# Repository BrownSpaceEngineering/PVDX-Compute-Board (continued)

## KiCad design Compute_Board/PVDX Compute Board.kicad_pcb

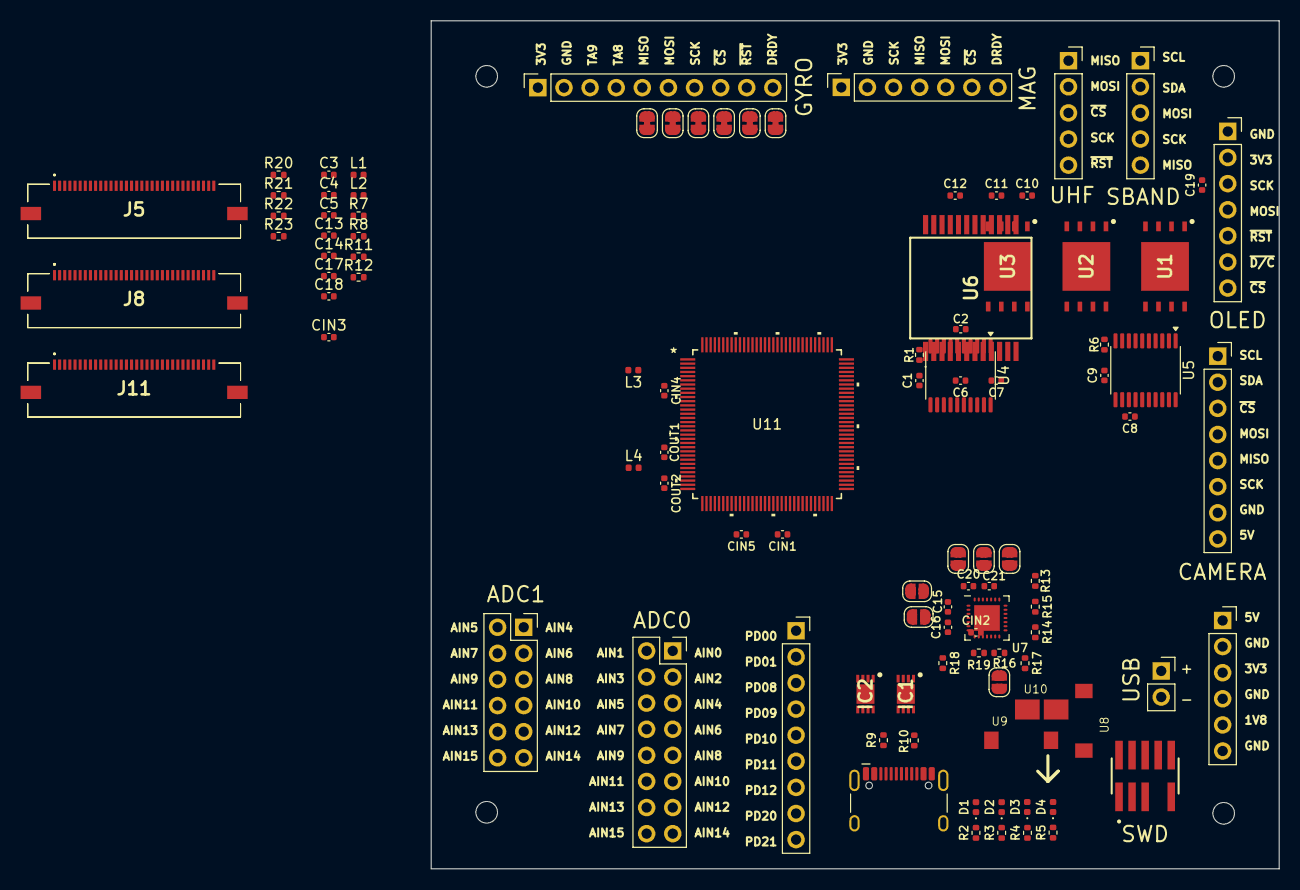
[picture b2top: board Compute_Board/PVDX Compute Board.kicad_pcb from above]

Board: 4 copper layers, 82.5 x 82.5 mm, 104 parts (0 on the bottom side), 161 nets, no tracks yet.

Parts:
C1, C2, C3, C4, C5, C8, C9, C12, C16, C21: 0.1 uF; C_0402_1005Metric
C6, C7, C15, C20: 10 uF; C_0402_1005Metric
C10, C11: 1 uF; C_0402_1005Metric
C13, C14, C17, C18, C19: 4.7 uF; C_0402_1005Metric
CIN1: 1 uF; C_0402_1005Metric
CIN2, CIN3: 10 uF; C_0402_1005Metric
CIN4, CIN5: 100 nF; C_0402_1005Metric
COUT1: 4.7 uF; C_0402_1005Metric
COUT2: 100 nF; C_0402_1005Metric
D1: RED; LED_0402_1005Metric
D2: GREEN; LED_0402_1005Metric
D3, D4: ORANGE; LED_0402_1005Metric
H1, H2, H3, H4: MountingHole; MountingHole_2.1mm
IC1: MCP1603-330I_MC; MPC1603-330
IC2: MCP1603-180I_MC; MPC1603-180
J1: USB_C_Receptacle_USB2.0_14P; USB_C_Receptacle_HCTL_HC-TYPE-C-16P-01A
J2: FTSH-105-01-L-DV-007-K; SAMTEC_FTSH-105-01-L-DV-007-K
J3: Conn_01x08; PinSocket_1x08_P2.54mm_Vertical
J4, J14: Conn_01x07; PinSocket_1x07_P2.54mm_Vertical
J5, J8, J11: 505110-3291; Molex 505110-3291 32x0.5mm FPC
J6: Conn_02x06_Top_Bottom; PinSocket_2x06_P2.54mm_Vertical
J7: Conn_02x08_Counter_Clockwise; PinSocket_2x08_P2.54mm_Vertical
J9: Conn_01x10; PinSocket_1x10_P2.54mm_Vertical
J10: Conn_01x02; PinSocket_1x02_P2.54mm_Vertical
J12: Conn_01x09; PinSocket_1x09_P2.54mm_Vertical
J13, J16: Conn_01x05; PinSocket_1x05_P2.54mm_Vertical
J15: Conn_01x06; PinSocket_1x06_P2.54mm_Vertical
JP1, JP2, JP3, JP4, JP5, JP6: SolderJumper_2_Open; SolderJumper-2_P1.3mm_Open_RoundedPad1.0x1.5mm
JP7, JP8, JP9, JP10, JP11, JP12: SolderJumper_2_Bridged; SolderJumper-2_P1.3mm_Bridged_RoundedPad1.0x1.5mm
L1, L2: 4.7 uH; L_0402_1005Metric
L3, L4: 10 uH; L_0402_1005Metric
R1, R6: 10K; R_0402_1005Metric
R2, R3, R4, R5: 1K; R_0402_1005Metric
R7, R8: 0; R_0402_1005Metric
R9, R10: 5.1K; R_0402_1005Metric
R11, R12: 22; R_0402_1005Metric
R13: 33k; R_0402_1005Metric
R14, R15, R16, R17, R18, R19: 121; R_0402_1005Metric
R20, R21, R22, R23: 10k; R_0402_1005Metric
U1, U2, U3: EM008LX; EM008LXQADG13IS1T
U4, U5: TXS0108EPW; TSSOP-20_4.4x6.5mm_P0.65mm
U6: SCH16T-K01; SCH16TK011
U7: MagI2C
U8, U9: Sen-XY-f
U10: Sen-Z-f
U11: SAMD51; TQFP128_14X14MC_MCH

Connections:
+1V8: C2.1, C3.2, C4.2, C5.2, C9.1, C18.1, IC2.4 (VFB/VOUT), J15.5, L2.2, U1.8 (VDD), U2.8 (VDD), U3.8 (VDD), U4.2 (VCCA), U5.2 (VCCA)
+3V3: C1.1, C6.1, C8.1, C11.1, C12.1, C17.1, C19.2, C20.2, C21.2, CIN1.1, CIN2.1, CIN5.1, D2.2 (A), IC1.4 (VFB/VOUT), J2.01, J4.2, J9.1, J14.1, J15.3, JP1.1 (A), L1.2, L3.1, R7.1, R8.1, U4.19 (VCCB), U5.19 (VCCB), U6.8 (V3P3), U6.17 (V3P3), U6.18 (VDDIO), U11.32 (VDDIOB), U11.37 (VDDIOB), U11.46 (VDDIO), U11.54 (VDDIO), U11.65 (VDDIO), U11.79 (VDDIO), U11.91 (VDDIO), U11.97 (VDDIO), U11.107 (VDDIO), U11.118 (VDDIO)
+5V: C13.1, C14.1, IC1.3 (~SHDN), IC1.7 (VIN), IC2.3 (~SHDN), IC2.7 (VIN), J1.A4 (VBUS), J1.A9 (VBUS), J1.B4 (VBUS), J1.B9 (VBUS), J3.8, J15.1, R20.1, R21.1, R22.1, R23.1
ADC0 AIN0: J5.3, J7.1, U11.9 (PA02)
ADC0 AIN1: J5.4, J7.2, U11.10 (PA03)
ADC0 AIN2: J7.3, J8.9, U11.19 (PB08)
ADC0 AIN3: J7.4, J8.10, U11.20 (PB09)
ADC0 AIN4: J5.5, J7.5, U11.21 (PA04)
ADC0 AIN5: J5.6, J7.6, U11.22 (PA05)
ADC0 AIN6: J5.7, J7.7, U11.23 (PA06)
ADC0 AIN7: J5.8, J7.8, U11.24 (PA07)
ADC0 AIN8: J5.9, J7.9, U11.33 (PA08)
ADC0 AIN9: J5.10, J7.10, U11.34 (PA09)
ADC0 AIN10: J5.11, J7.11, U11.35 (PA10)
ADC0 AIN11: J5.12, J7.12, U11.36 (PA11)
ADC0 AIN12: J7.13, J8.1, U11.125 (PB00)
ADC0 AIN13: J7.14, J8.2, U11.126 (PB01)
ADC0 AIN14: J7.15, J8.3, U11.127 (PB02)
ADC0 AIN15: J7.16, J8.4, U11.128 (PB03)
ADC1 AIN4: J6.1, J11.3, U11.7 (PC02)
ADC1 AIN5: J6.2, J11.4, U11.8 (PC03)
ADC1 AIN6: J6.3, J8.5, U11.11 (PB04)
ADC1 AIN7: J6.4, J8.6, U11.12 (PB05)
ADC1 AIN8: J6.5, J8.7, U11.17 (PB06)
ADC1 AIN9: J6.6, J8.8, U11.18 (PB07)
ADC1 AIN10: J6.7, J11.1, U11.3 (PC00)
ADC1 AIN11: J6.8, J11.2, U11.4 (PC01)
ADC1 AIN12: J6.9, J11.31, U11.123 (PC30)
ADC1 AIN13: J6.10, J11.32, U11.124 (PC31)
ADC1 AIN14: J6.11, J12.1, U11.13 (PD00)
ADC1 AIN15: J6.12, J12.2, U11.16 (PD01)
CAMERA MISO: J3.5, J5.15, U11.62 (PA14)
CAMERA MOSI: J3.4, J8.27, U11.102 (PB26)
CAMERA SCK: J3.6, J8.28, U11.103 (PB27)
CAMERA SCL: J3.1, J12.3, R20.2, U11.47 (PD08)
CAMERA SDA: J3.2, J12.4, R21.2, U11.48 (PD09)
CAMERA ~CS: J3.3, J11.15, U11.58 (PC14)
GND: C1.2, C2.2, C3.1, C4.1, C5.1, C6.2, C7.2, C8.2, C9.2, C10.2, C11.2, C12.2, C13.2, C14.2, C15.1, C16.1, C17.2, C18.2, C19.1, C20.1, C21.1, CIN1.2, CIN2.2, CIN3.2, CIN4.2, CIN5.2, COUT1.2, COUT2.2, IC1.8 (GND), IC1.9 (EP), IC2.8 (GND), IC2.9 (EP), J1.A1 (GND), J1.A12 (GND), J1.B1 (GND), J1.B12 (GND), J1.S1 (SHIELD), J2.03, J2.05, J3.7, J4.1, J5.27, J5.29, J5.30, J5.MP1, J5.MP2, J8.MP1, J8.MP2, J9.2, J9.3, J9.4, J11.9, J11.10, J11.30, J11.MP1, J11.MP2, J14.2, J15.2, J15.4, J15.6, R1.2, R2.1, R3.1, R4.1, R5.1, R6.2, R9.2, R10.2, R13.2, U1.4 (VSS), U2.4 (VSS), U3.4 (VSS), U4.11 (GND), U5.11 (GND), U6.1 (HEATSINK), U6.5 (RESERVED), U6.7 (RESERVED), U6.9 (GND), U6.12 (GND), U6.13 (GND), U6.16 (GND), U6.24 (HEATSINK), U7.2 (RES), U7.5 (AVSS), U7.19 (DVSS), U7.20 (RES), U7.22 (I2C), U11.5 (GND), U11.14 (GNDANA), U11.25 (GNDANA), U11.31 (GND), U11.38 (GND), U11.45 (GND), U11.53 (GND), U11.64 (GND), U11.78 (GND), U11.90 (GND), U11.96 (GND), U11.106 (GND), U11.116 (GNDIO)
GYRO DRDY: J11.23, JP12.2 (B), U6.20 (DRY_SYNC), U11.76 (PC22)
GYRO ~CS: J11.21, JP10.2 (B), U6.22 (CS), U11.74 (PC20)
GYRO ~RST: J11.22, JP11.2 (B), U6.6 (EXTRESN), U11.75 (PC21)
LED ORANGE 1: D3.2 (A), J11.16, U11.59 (PC15)
LED ORANGE 2: D4.2 (A), J5.16, U11.63 (PA15)
LED RED: D1.2 (A), J5.20, U11.69 (PA19)
MAG DRDY: J11.11, J14.7, JP6.1 (A), U11.52 (PC10)
MAG ~CS: J11.20, J14.6, JP5.1 (A), U11.73 (PC19)
MAG/GYRO MISO: J8.15, J14.4, JP3.1 (A), JP7.2 (B), U6.19 (MISO), U11.43 (PB14)
MAG/GYRO MOSI: J5.14, J14.5, JP4.1 (A), JP8.2 (B), U6.23 (MOSI), U11.61 (PA13)
MAG/GYRO SCK: J5.13, J14.3, JP2.1 (A), JP9.2 (B), U6.21 (SCK), U11.60 (PA12)
MRAM 1 ~CS: J11.5, U4.15 (B5), U11.27 (PC04)
MRAM 1 ~CS 1V8: U1.1 (~CS), U4.6 (A5)
MRAM 1 ~RESET: J11.6, U4.16 (B4), U11.28 (PC05)
MRAM 1 ~RESET 1V8: U1.7 (IO3/~RESET), U4.5 (A4)
MRAM 1 ~WP: J8.13, U4.14 (B6), U11.41 (PB12)
MRAM 1 ~WP 1V8: U1.3 (~WP/IO2), U4.7 (A6)
MRAM 2 ~CS: J11.7, U5.20 (B1), U11.29 (PC06)
MRAM 2 ~CS 1V8: U2.1 (~CS), U5.1 (A1)
MRAM 2 ~RESET: J11.8, U4.13 (B7), U11.30 (PC07)
MRAM 2 ~RESET 1V8: U2.7 (IO3/~RESET), U4.8 (A7)
MRAM 2 ~WP: J8.14, U5.18 (B2), U11.42 (PB13)
MRAM 2 ~WP 1V8: U2.3 (~WP/IO2), U5.3 (A2)
MRAM 3 ~CS: J8.11, U5.17 (B3), U11.39 (PB10)
MRAM 3 ~CS 1V8: U3.1 (~CS), U5.4 (A3)
MRAM 3 ~RESET: J8.12, U5.15 (B5), U11.40 (PB11)
MRAM 3 ~RESET 1V8: U3.7 (IO3/~RESET), U5.6 (A5)
MRAM 3 ~WP: J8.16, U5.16 (B4), U11.44 (PB15)
MRAM 3 ~WP 1V8: U3.3 (~WP/IO2), U5.5 (A4)
MRAM MISO: J11.19, U4.18 (B2), U11.72 (PC18)
MRAM MISO 1V8: U1.2 (IO1), U2.2 (IO1), U3.2 (IO1), U4.3 (A2)
MRAM MOSI: J8.25, U4.20 (B1), U11.100 (PB24)
MRAM MOSI 1V8: U1.5 (IO0), U2.5 (IO0), U3.5 (IO0), U4.1 (A1)
MRAM SCK: J8.26, U4.17 (B3), U11.101 (PB25)
MRAM SCK 1V8: U1.6 (CK), U2.6 (CK), U3.6 (CK), U4.4 (A3)
unnamed: CIN3.1, CIN4.1, L3.2, U11.6 (VDDANA), U11.15 (VDDANA), U11.26 (VDDANA)
unnamed: D1.1 (K), R2.2
unnamed: D2.1 (K), R3.2
unnamed: D3.1 (K), R4.2
unnamed: D4.1 (K), R5.2
unnamed: IC1.1 (LX), L1.1
unnamed: IC2.1 (LX), L2.1
unnamed: J1.A5 (CC1), R9.1
unnamed: J1.B5 (CC2), R10.1
unnamed: J1.A6 (D+), J1.B6 (D+), R12.1
unnamed: J1.A7 (D-), J1.B7 (D-), R11.1
unnamed: J9.5, JP7.1 (A)
unnamed: J9.6, JP8.1 (A)
unnamed: J9.7, JP9.1 (A)
unnamed: J9.8, JP10.1 (A)
unnamed: J9.9, JP11.1 (A)
unnamed: J9.10, JP12.1 (A)
unnamed: C15.2, C16.2, JP1.2 (B), U7.4 (AVDD), U7.14 (DVDD), U7.26 (DVDD)
unnamed: JP2.2 (B), U7.27 (SCLK)
unnamed: JP3.2 (B), U7.28 (MISO)
unnamed: JP4.2 (B), U7.1 (MOSI)
unnamed: JP5.2 (B), U7.3 (SSN)
unnamed: JP6.2 (B), U7.23 (DRDY)
unnamed: R1.1, U4.10 (OE)
unnamed: R6.1, U5.10 (OE)
unnamed: R8.2, U6.4 (TA8)
unnamed: R7.2, U6.3 (TA9)
unnamed: C7.1, U6.10 (VREGA2), U6.11 (VREGA)
unnamed: C10.1, U6.14 (VREGD2), U6.15 (VREGD)
unnamed: R13.1, U7.25 (REXT)
unnamed: R15.1, U7.18 (XDRVN)
unnamed: R14.1, U7.15 (XDVRP)
unnamed: R15.2, U7.17 (XNN), U8.2
unnamed: R14.2, U7.16 (XNP), U8.1
unnamed: R17.1, U7.13 (YDRVN)
unnamed: R16.1, U7.10 (YDRVP)
unnamed: R16.2, R17.2, U7.11 (YNP), U7.12 (YNN), U9.1, U9.2
unnamed: R19.1, U7.9 (ZDRVN)
unnamed: R18.1, U7.6 (ZDRVP)
unnamed: R19.2, U7.8 (ZNN), U10.2
unnamed: R18.2, U7.7 (ZNP), U10.1
unnamed: COUT1.1, COUT2.1, L4.1, U11.115 (VDDCORE)
unnamed: L4.2, U11.117 (VSW)
OLED MISO: J5.19, U11.68 (PA18)
OLED MOSI: J4.4, J5.1, U11.1 (PA00)
OLED SCK: J4.3, J5.2, U11.2 (PA01)
OLED ~CS: J4.7, J11.12, U11.55 (PC11)
OLED ~D/C: J4.6, J12.7, U11.51 (PD12)
OLED ~RST: J4.5, J12.6, U11.50 (PD11)
PA20: J5.21, U11.88 (PA20)
PA21: J5.22, U11.89 (PA21)
PA22: J5.23, U11.92 (PA22)
PA23: J5.24, U11.93 (PA23)
PA24: J5.25, U11.94 (PA24)
PA25: J5.26, U11.95 (PA25)
PA27: J5.28, U11.113 (PA27)
PB19: J8.20, U11.85 (PB19)
PB20: J8.21, U11.86 (PB20)
PB21: J8.22, U11.87 (PB21)
PB22: J8.23, U11.98 (PB22)
PB23: J8.24, U11.99 (PB23)
PB28: J8.29, U11.104 (PB28)
PB29: J8.30, U11.105 (PB29)
PB30: J8.31, U11.121 (PB30)
PB31: J8.32, U11.122 (PB31)
PC23: J11.24, U11.77 (PC23)
PC24: J11.25, U11.108 (PC24)
PC25: J11.26, U11.109 (PC25)
PC26: J11.27, U11.110 (PC26)
PC27: J11.28, U11.111 (PC27)
PC28: J11.29, U11.112 (PC28)
PD20: J12.8, U11.80 (PD20)
PD21: J12.9, U11.81 (PD21)
SBAND MISO: J8.19, J16.5, U11.84 (PB18)
SBAND MOSI: J8.17, J16.3, U11.82 (PB16)
SBAND SCK: J8.18, J16.4, U11.83 (PB17)
SBAND SCL: J5.17, J16.1, U11.66 (PA16)
SBAND SDA: J5.18, J16.2, R22.2, R23.2, U11.67 (PA17)
SWCLK: J2.04, J5.31, U11.119 (PA30)
SWD ~RESET: J2.10, U11.114 (~RESET)
SWDIO: J2.02, J5.32, U11.120 (PA31)
UHF MISO: J12.5, J13.1, U11.49 (PD10)
UHF MOSI: J11.13, J13.2, U11.56 (PC12)
UHF SCK: J11.14, J13.4, U11.57 (PC13)
UHF ~CS: J11.17, J13.3, U11.70 (PC16)
UHF ~RESET: J11.18, J13.5, U11.71 (PC17)
USB D+: J10.2, R12.2
USB D-: J10.1, R11.2

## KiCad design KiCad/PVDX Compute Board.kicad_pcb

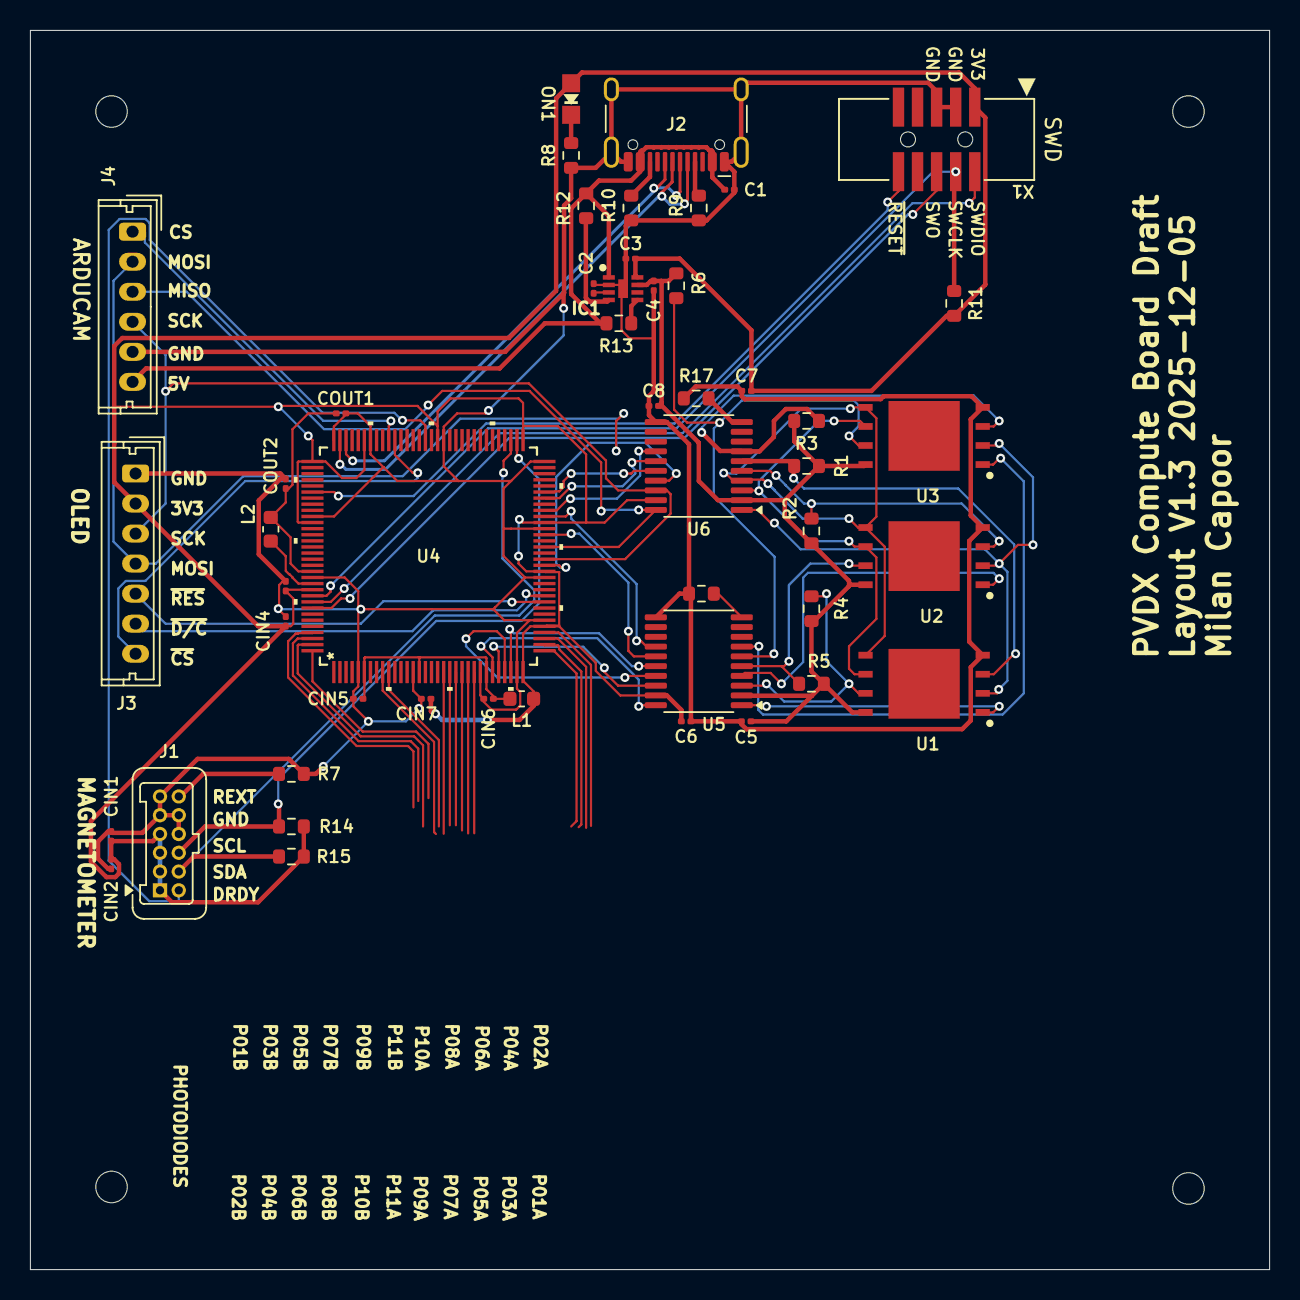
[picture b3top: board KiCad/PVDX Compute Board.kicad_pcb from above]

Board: 2 copper layers, 82.5 x 82.5 mm, 53 parts (0 on the bottom side), 53 nets.

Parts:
C1: 10uF; C_0201_0603Metric
C2: 0.1uF; C_0201_0603Metric
C3, C4: 2.2uF; C_0201_0603Metric
C5, C6, C7, C8: 0.1 uF; C_0201_0603Metric
CIN1, CIN4, CIN5: 10 uF; C_0201_0603Metric
CIN2: 0.1 uF; C_0201_0603Metric
CIN3: 1 uF; C_0201_0603Metric
CIN6, CIN7: 100 nF; C_0201_0603Metric
COUT1: 4.7 uF; C_0201_0603Metric
COUT2: 100 nF; C_0201_0603Metric
H1, H2, H3, H4: MountingHole; MountingHole_2.1mm
IC1: MIC5350-SGYMT-TR; SON50P200X200X60-9N
J1: Conn_02x06_Counter_Clockwise; Harwin_Gecko-G125-FVX1205L0X_2x06_P1.25mm_Vertical
J2: USB_C_Receptacle_USB2.0_14P; USB_C_Receptacle_HCTL_HC-TYPE-C-16P-01A
J3: Conn_01x07; Molex_Micro-Latch_53253-0770_1x07_P2.00mm_Vertical
J4: Conn_01x06; Molex_Micro-Latch_53253-0670_1x06_P2.00mm_Vertical
L1, L2: 10 uH; L_0603_1608Metric
ON1: GREEN; CHIPLED_0805_NOOUTLINE
R1, R2, R3, R4, R5, R6, R12, R13, R14, R15, R16, R17: 10K; R_0603_1608Metric
R7: 33K; R_0603_1608Metric
R8, R11: 1K; R_0603_1608Metric
R9, R10: 5.1K; R_0603_1608Metric
U1, U2, U3: EM008LX; EM008LXQADG13IS1T
U4: SAMD51; TQFP128_14X14MC_MCH
U5, U6: TXS0108EPW; TSSOP-20_4.4x6.5mm_P0.65mm
X1: 2x5 0.05" SWD; 2X05_1.27MM_BOX_POSTS

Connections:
1V8: C4.1, C5.1, C8.1, IC1.7 (VOUT2), R1.1, R2.1, R3.1, R4.2, R5.2, R6.2, U1.8 (VDD), U2.8 (VDD), U3.8 (VDD), U5.2 (VCCA), U6.2 (VCCA)
3V3: C3.1, C6.1, C7.1, CIN1.1, CIN2.1, CIN3.1, CIN4.1, CIN7.1, IC1.8 (VOUT1), J1.1, J1.2, J1.3, J1.4, J3.2, L1.1, ON1.A, R11.2, R14.2, R15.2, U4.32 (VDDIOB), U4.37 (VDDIOB), U4.46 (VDDIO), U4.54 (VDDIO), U4.65 (VDDIO), U4.79 (VDDIO), U4.91 (VDDIO), U4.97 (VDDIO), U4.107 (VDDIO), U4.118 (VDDIO), U5.19 (VCCB), U6.19 (VCCB), X1.1 (VCC)
5V: C1.1, IC1.1 (VIN), J2.A4 (VBUS), J2.A9 (VBUS), J2.B4 (VBUS), J2.B9 (VBUS), J4.6, R12.1, R13.1
/Peripherals/REXT: J1.12, R7.1
GND: C1.2, C2.2, C3.2, C4.2, C5.2, C6.2, C7.2, C8.2, CIN1.2, CIN2.2, CIN3.2, CIN4.2, CIN5.2, CIN6.2, CIN7.2, COUT1.2, COUT2.2, IC1.2 (GND_1), IC1.9 (GND_2), J1.5, J1.6, J1.10, J1.11, J2.A1 (GND), J2.A12 (GND), J2.B1 (GND), J2.B12 (GND), J2.S1 (SHIELD), J3.1, J4.5, R7.2, R8.1, R9.2, R10.2, R16.2, R17.2, U1.4 (VSS), U2.4 (VSS), U3.4 (VSS), U4.5 (GND), U4.14 (GNDANA), U4.25 (GNDANA), U4.31 (GND), U4.38 (GND), U4.45 (GND), U4.53 (GND), U4.64 (GND), U4.78 (GND), U4.90 (GND), U4.96 (GND), U4.106 (GND), U4.116 (GNDIO), U5.11 (GND), U6.11 (GND), X1.3 (GND@1), X1.5 (GND@2)
unnamed: CIN5.1, CIN6.1, L1.2, U4.6 (VDDANA), U4.15 (VDDANA), U4.26 (VDDANA)
unnamed: C2.1, IC1.3 (BYP)
unnamed: IC1.5 (EN1), R13.2
unnamed: IC1.4 (EN2), R12.2
unnamed: J2.A5 (CC1), R9.1
unnamed: J2.B5 (CC2), R10.1
unnamed: ON1.C, R8.2
unnamed: COUT1.1, COUT2.1, L2.1, U4.115 (VDDCORE)
unnamed: L2.2, U4.117 (VSW)
unnamed: R16.1, U5.10 (OE)
unnamed: R17.1, U6.10 (OE)
PA16 (SCL): J1.9, R14.1, U4.66 (PA16)
PA17 (SDA): J1.8, R15.1, U4.67 (PA17)
PB12: J3.5, U4.41 (PB12)
PB13: J3.6, U4.42 (PB13)
PB20: J3.7, U4.86 (PB20)
PB21: J4.1, U4.87 (PB21)
PC04: U4.27 (PC04), U5.20 (B1)
PC04 1V8: U1.1 (~CS), U5.1 (A1)
PC05: U4.28 (PC05), U5.18 (B2)
PC05 1V8: R4.1, U1.7 (IO3/~RESET), U5.3 (A2)
PC06: U4.29 (PC06), U5.17 (B3)
PC06 1V8: U2.1 (~CS), U5.4 (A3)
PC07: U4.30 (PC07), U5.16 (B4)
PC07 1V8: R5.1, U2.7 (IO3/~RESET), U5.5 (A4)
PC10: U4.52 (PC10), U5.15 (B5)
PC10 1V8: R6.1, U3.7 (IO3/~RESET), U5.6 (A5)
PC11: U4.55 (PC11), U5.14 (B6)
PC11 1V8: U3.1 (~CS), U5.7 (A6)
PC12: U4.56 (PC12), U6.14 (B6)
PC12 1V8: R3.2, U3.3 (~WP/IO2), U6.7 (A6)
PC14: U4.58 (PC14), U6.15 (B5)
PC14 1V8: R1.2, U1.3 (~WP/IO2), U6.6 (A5)
PC15: U4.59 (PC15), U6.16 (B4)
PC15 1V8: R2.2, U2.3 (~WP/IO2), U6.5 (A4)
PD08 (MOSI): J3.4, J4.2, U4.47 (PD08), U6.17 (B3)
PD08 (MOSI) 1V8: U1.5 (IO0), U2.5 (IO0), U3.5 (IO0), U6.4 (A3)
PD09 (SCK): J3.3, J4.4, U4.48 (PD09), U6.18 (B2)
PD09 (SCK) 1V8: U1.6 (CK), U2.6 (CK), U3.6 (CK), U6.3 (A2)
PD11 (MISO): J4.3, U4.50 (PD11), U6.20 (B1)
PD11 (MISO) 1V8: U1.2 (IO1), U2.2 (IO1), U3.2 (IO1), U6.1 (A1)
PD21: J1.7, U4.81 (PD21)
SWCLK: R11.1, U4.119 (PA30), X1.4 (SWDCLK)
SWD ~RESET: U4.102 (PB26), X1.10 (NRESET)
SWDIO: U4.120 (PA31), X1.2 (SWDIO)
SWO: U4.121 (PB30), X1.6 (SWO)
USB D+: J2.A6 (D+), J2.B6 (D+), U4.94 (PA24)
USB D-: J2.A7 (D-), J2.B7 (D-), U4.95 (PA25)

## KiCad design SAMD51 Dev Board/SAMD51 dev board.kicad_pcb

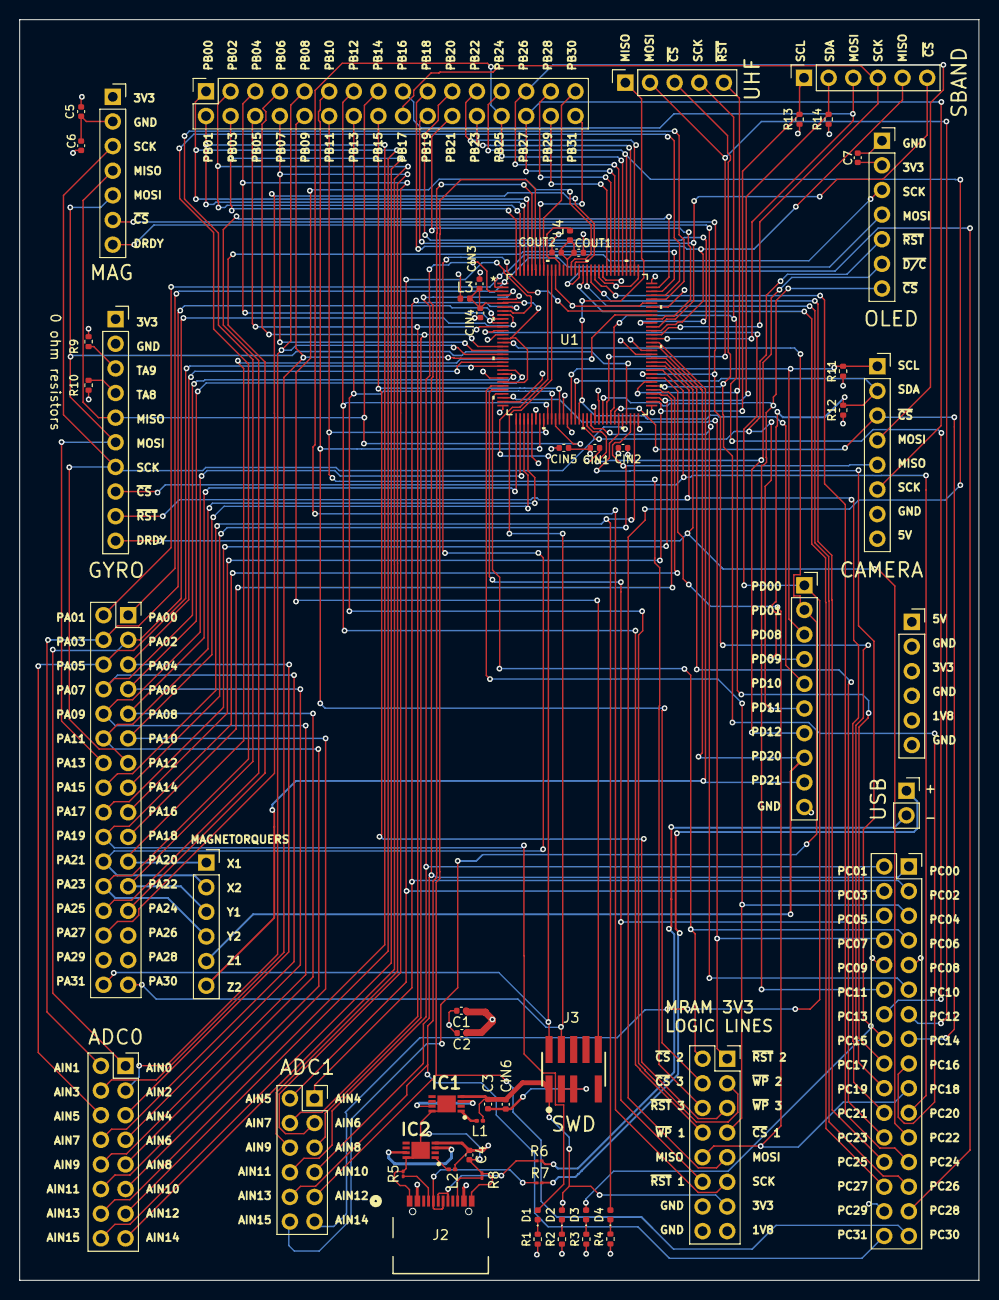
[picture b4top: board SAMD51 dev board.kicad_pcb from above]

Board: 4 copper layers, 98.9 x 130.0 mm, 58 parts (0 on the bottom side), 121 nets.

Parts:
C1, C2, C3, C4, C7: 4.7 uF; C_0402_1005Metric
C5: 10 uF; C_0402_1005Metric
C6: 0.1 uF; C_0402_1005Metric
CIN1, CIN2, CIN3: 10 uF; C_0402_1005Metric
CIN4, CIN5, CIN6: 100 nF; C_0402_1005Metric
COUT1: 4.7 uF; C_0402_1005Metric
COUT2: 100 nF; C_0402_1005Metric
D1: RED; LED_0402_1005Metric
D2: GREEN; LED_0402_1005Metric
D3, D4: ORANGE; LED_0402_1005Metric
IC1: MCP1603-330I_MC; MPC1603-330
IC2: MCP1603-180I_MC; MPC1603-180
J1: Conn_02x08_Top_Bottom; PinSocket_2x08_P2.54mm_Vertical
J2: USB4105-GF-A; USB4105_GCT
J3: FTSH-105-01-L-DV-007-K; SAMTEC_FTSH-105-01-L-DV-007-K
J4, J11: Conn_01x07; PinSocket_1x07_P2.54mm_Vertical
J5, J10, J14: Conn_02x16_Top_Bottom; PinSocket_2x16_P2.54mm_Vertical
J6: Conn_02x06_Top_Bottom; PinSocket_2x06_P2.54mm_Vertical
J7: Conn_02x08_Counter_Clockwise; PinSocket_2x08_P2.54mm_Vertical
J8, J17: Conn_01x10; PinSocket_1x10_P2.54mm_Vertical
J9: Conn_01x02; PinSocket_1x02_P2.54mm_Vertical
J12: Conn_01x05; PinSocket_1x05_P2.54mm_Vertical
J13: Conn_01x08; PinSocket_1x08_P2.54mm_Vertical
J15, J16, J19: Conn_01x06; PinSocket_1x06_P2.54mm_Vertical
L1, L2: 4.7uH; L_0201_0603Metric
L3, L4: 10 uH; L_0402_1005Metric
R1, R2, R3, R4: 1K; R_0402_1005Metric
R5, R8: 5.1k; R_01005_0402Metric
R6, R7: 22; R_01005_0402Metric
R9, R10: 0; R_0402_1005Metric
R11, R12, R13, R14: 10k; R_0402_1005Metric
U1: SAMD51; TQFP128_14X14MC_MCH-L

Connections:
+1V8: C4.1, IC2.4 (VFB/VOUT), J1.15, J16.5, L2.1
+3V3: C3.1, C5.2, C6.2, C7.2, CIN1.1, CIN2.1, CIN5.1, CIN6.1, D2.2 (A), IC1.4 (VFB/VOUT), J1.13, J3.01, J4.1, J8.1, J11.2, J16.3, L1.1, L3.1, R9.2, R10.2, U1.32 (VDDIOB), U1.37 (VDDIOB), U1.46 (VDDIO), U1.54 (VDDIO), U1.65 (VDDIO), U1.79 (VDDIO), U1.91 (VDDIO), U1.97 (VDDIO), U1.107 (VDDIO), U1.118 (VDDIO)
+5V: C1.1, C2.1, IC1.3 (~SHDN), IC1.7 (VIN), IC2.3 (~SHDN), IC2.7 (VIN), J2.A4-B9 (VBUS), J2.B4-A9 (VBUS), J13.8, J16.1, R11.1, R12.1, R13.1, R14.1
ADC0 AIN0: J5.3, J7.1, U1.9 (PA02/AIN00)
ADC0 AIN1: J5.4, J7.2, U1.10 (PA03/AIN01)
ADC0 AIN2: J7.3, J10.9, U1.19 (PB08/AIN02)
ADC0 AIN3: J7.4, J10.10, U1.20 (PB09/AIN03)
ADC0 AIN4: J5.5, J7.5, U1.21 (PA04/AIN04)
ADC0 AIN5: J5.6, J7.6, U1.22 (PA05/AIN05)
ADC0 AIN6: J5.7, J7.7, U1.23 (PA06/AIN06)
ADC0 AIN7: J5.8, J7.8, U1.24 (PA07/AIN07)
ADC0 AIN8: J5.9, J7.9, U1.33 (PA08/AIN08)
ADC0 AIN9: J5.10, J7.10, U1.34 (PA09/AIN09)
ADC0 AIN10: J5.11, J7.11, U1.35 (PA10/AIN10)
ADC0 AIN11: J5.12, J7.12, U1.36 (PA11/AIN11)
ADC0 AIN12: J7.13, J10.1, U1.125 (PB00/AIN12)
ADC0 AIN13: J7.14, J10.2, U1.126 (PB01/AIN13)
ADC0 AIN14: J7.15, J10.3, U1.127 (PB02/AIN14)
ADC0 AIN15: J7.16, J10.4, U1.128 (PB03/AIN15)
ADC1 AIN4: J6.1, J14.3, U1.7 (PC02)
ADC1 AIN5: J6.2, J14.4, U1.8 (PC03)
ADC1 AIN6: J6.3, J10.5, U1.11 (PB04)
ADC1 AIN7: J6.4, J10.6, U1.12 (PB05)
ADC1 AIN8: J6.5, J10.7, U1.17 (PB06)
ADC1 AIN9: J6.6, J10.8, U1.18 (PB07)
ADC1 AIN10: J6.7, J14.1, U1.3 (PC00)
ADC1 AIN11: J6.8, J14.2, U1.4 (PC01)
ADC1 AIN12: J6.9, J14.31, U1.123 (PC30)
ADC1 AIN13: J6.10, J14.32, U1.124 (PC31)
ADC1 AIN14: J6.11, J17.1, U1.13 (PD00)
ADC1 AIN15: J6.12, J17.2, U1.16 (PD01)
CAMERA MISO: J5.15, J13.5, U1.62 (PA14)
CAMERA MOSI: J10.27, J13.4, U1.102 (PB26)
CAMERA SCK: J10.28, J13.6, U1.103 (PB27)
CAMERA SCL: J13.1, J17.3, R11.2, U1.47 (PD08)
CAMERA SDA: J13.2, J17.4, R12.2, U1.48 (PD09)
CAMERA ~CS: J13.3, J14.15, U1.58 (PC14)
GND: C1.2, C2.2, C3.2, C4.2, C5.1, C6.1, C7.1, CIN1.2, CIN2.2, CIN3.2, CIN4.2, CIN5.2, CIN6.2, COUT1.2, COUT2.2, IC1.8 (GND), IC1.9 (EP), IC2.8 (GND), IC2.9 (EP), J1.14, J1.16, J2.A1-B12 (GND), J2.B1-A12 (GND), J3.03, J3.05, J4.2, J5.27, J5.29, J5.30, J8.2, J11.1, J13.7, J14.9, J14.10, J14.30, J16.2, J16.4, J16.6, J17.10, R1.1, R2.1, R3.1, R4.1, R5.2, R8.2, U1.5 (GND), U1.14 (GNDANA), U1.25 (GNDANA), U1.31 (GND), U1.38 (GND), U1.45 (GND), U1.53 (GND), U1.64 (GND), U1.78 (GND), U1.90 (GND), U1.96 (GND), U1.106 (GND)
GYRO DRDY: J8.10, J14.23, U1.76 (PC22)
GYRO ~CS: J8.8, J14.21, U1.74 (PC20)
GYRO ~RST: J8.9, J14.22, U1.75 (PC21)
LED ORANGE 1: D3.2 (A), J14.16, U1.59 (PC15)
LED ORANGE 2: D4.2 (A), J5.16, U1.63 (PA15)
LED RED: D1.2 (A), J5.20, U1.69 (PA19)
MAG DRDY: J4.7, J14.11, U1.52 (PC10)
MAG ~CS: J4.6, J14.20, U1.73 (PC19)
MAG/GYRO MISO: J4.4, J8.5, J10.15, U1.43 (PB14)
MAG/GYRO MOSI: J4.5, J5.14, J8.6, U1.61 (PA13)
MAG/GYRO SCK: J4.3, J5.13, J8.7, U1.60 (PA12)
MRAM 1 ~CS: J1.7, J14.5, U1.27 (PC04)
MRAM 1 ~RESET: J1.12, J14.6, U1.28 (PC05)
MRAM 1 ~WP: J1.8, J10.13, U1.41 (PB12)
MRAM 2 ~CS: J1.2, J14.7, U1.29 (PC06)
MRAM 2 ~RESET: J1.1, J14.8, U1.30 (PC07)
MRAM 2 ~WP: J1.3, J10.14, U1.42 (PB13)
MRAM 3 ~CS: J1.4, J10.11, U1.39 (PB10)
MRAM 3 ~RESET: J1.6, J10.12, U1.40 (PB11)
MRAM 3 ~WP: J1.5, J10.16, U1.44 (PB15)
MRAM MISO: J1.10, J14.19, U1.72 (PC18)
MRAM MOSI: J1.9, J10.25, U1.100 (PB24)
MRAM SCK: J1.11, J10.26, U1.101 (PB25)
MTQ_X_IN1: J5.21, J19.1, U1.88 (PA20)
MTQ_X_IN2: J5.22, J19.2, U1.89 (PA21)
MTQ_Y_IN1: J5.23, J19.3, U1.92 (PA22)
MTQ_Y_IN2: J5.24, J19.4, U1.93 (PA23)
MTQ_Z_IN1: J17.8, J19.5, U1.80 (PD20)
MTQ_Z_IN2: J17.9, J19.6, U1.81 (PD21)
unnamed: CIN3.1, CIN4.1, L3.2, U1.6 (VDDANA), U1.15 (VDDANA), U1.26 (VDDANA)
unnamed: D1.1 (K), R1.2
unnamed: D2.1 (K), R2.2
unnamed: D3.1 (K), R3.2
unnamed: D4.1 (K), R4.2
unnamed: IC1.1 (LX), L1.2
unnamed: IC2.1 (LX), L2.2
unnamed: J2.A5 (CC1), R5.1
unnamed: J2.B5 (CC2), R8.1
unnamed: J2.A7 (DN1), J2.B7 (DN2), R7.1
unnamed: J2.A6 (DP1), J2.B6 (DP2), R6.1
unnamed: J8.3, R9.1
unnamed: J8.4, R10.1
unnamed: COUT1.1, COUT2.1, L4.1, U1.115 (VDDCORE)
unnamed: L4.2, U1.117 (VSW)
OLED MISO: J5.19, U1.68 (PA18)
OLED MOSI: J5.1, J11.4, U1.1 (PA00)
OLED SCK: J5.2, J11.3, U1.2 (PA01)
OLED ~CS: J11.7, J14.12, U1.55 (PC11)
OLED ~D/C: J11.6, J17.7, U1.51 (PD12)
OLED ~RST: J11.5, J17.6, U1.50 (PD11)
PA24: J5.25, U1.94 (PA24)
PA25: J5.26, U1.95 (PA25)
PA27: J5.28, U1.113 (PA27)
PB20: J10.21, U1.86 (PB20)
PB21: J10.22, U1.87 (PB21)
PB22: J10.23, U1.98 (PB22)
PB23: J10.24, U1.99 (PB23)
PB28: J10.29, U1.104 (PB28)
PB29: J10.30, U1.105 (PB29)
PB30: J10.31, U1.121 (PB30)
PB31: J10.32, U1.122 (PB31)
PC23: J14.24, U1.77 (PC23)
PC24: J14.25, U1.108 (PC24)
PC25: J14.26, U1.109 (PC25)
PC26: J14.27, U1.110 (PC26)
PC27: J14.28, U1.111 (PC27)
PC28: J14.29, U1.112 (PC28)
SBAND MISO: J10.19, J15.5, U1.84 (PB18)
SBAND MOSI: J10.17, J15.3, U1.82 (PB16)
SBAND SCK: J10.18, J15.4, U1.83 (PB17)
SBAND SCL: J5.17, J15.1, R13.2, U1.66 (PA16)
SBAND SDA: J5.18, J15.2, R14.2, U1.67 (PA17)
SBAND ~CS: J10.20, J15.6, U1.85 (PB19)
SWCLK: J3.04, J5.31, U1.119 (PA30)
SWD ~RESET: J3.10, U1.114 (~RESET)
SWDIO: J3.02, J5.32, U1.120 (PA31)
UHF MISO: J12.1, J17.5, U1.49 (PD10)
UHF MOSI: J12.2, J14.13, U1.56 (PC12)
UHF SCK: J12.4, J14.14, U1.57 (PC13)
UHF ~CS: J12.3, J14.17, U1.70 (PC16)
UHF ~RESET: J12.5, J14.18, U1.71 (PC17)
USB D+: J9.2, R6.2
USB D-: J9.1, R7.2

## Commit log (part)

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2025-10-12 Latest
2025-11-14 update draft to 11/13 version
2025-12-05 Redid layout to separate analog/digital traces
2026-03-06 updated pins to match new spec and exposed all pins
2026-04-07 reorganized repo and added samd breakout
2026-04-14 routed samd51 breakout
2026-04-30 Fix USBC and regulators on samd breakout board, changes need to be added to compute board.
2026-05-14 Update LED resistor values
